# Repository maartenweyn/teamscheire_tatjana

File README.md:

# Team Scheire Tatjana - Tinnitus

Aflevering op VRTNu: [https://vrtnu.page.link/GqeyBG1gsRzztzNG9](https://vrtnu.page.link/GqeyBG1gsRzztzNG9)

Uitleg over de oplossing in deze podcast: [https://soundcloud.com/nerdlandmakertalk/09-maarten-weyn](https://soundcloud.com/nerdlandmakertalk/09-maarten-weyn)

# Geluidsmetingen

## 1. Wat is geluid?

**Geluid** is de **hoorbare verandering** van **luchtdruk** , of als je helemaal volledig wil zijn de verandering van de **dichtheid** van een **elastisch medium** , dat kan een **gas** zijn, een **vloeistof** of een **vaste** stof. En een geluidsbron veroorzaak verandering in de luchtdruk die zich in een golfbeweging door de lucht voortbewegen. Een luidspreker bijvoorbeeld zet een elektrisch signaal om in een beweging van een membraan. Die beweging zal dan een verandering in de luchtdruk veroorzaken.

Geluidsgolven tussen 20 Hz en 20 kHz, m.a.w. golven die 20 tot 20 000 keer per seconde bewegen kunnen door de mensen worden waargenomen. Boven 20 kHz hebben we wat we ultrasoon noemen.

Wist je dat geluid zich in lucht (bij 20°C en op zeeniveau) met ongeveer 343 m/s (of 1230 km/u) voortbeweegt, en in water van 20°C zelfs met 1482 m/s.

## 2. Wat is dan de geluidssterkte?

De **geluidsdruk** is het lokale drukverschil t.o.v. de atmosferische luchtdruk ten gevolge van een geluidsgolf. En dat wordt typisch in Pascal uitgedrukt.

Dit verschil wordt over een zeer kleine periode uitgemiddeld, men berekent de &quot;root mean square&quot; of de wortel van het gemiddelde van het kwadraat. Deze variatie is typisch zeer klein, de laagste waarde die nog hoorbaar is, is rond 2 \* 10-5 of 0.00002 Pa terwijl een explosie ongeveer 104 of 10000 kan zijn.

Daarom gebruik met een logaritmes waarde om de geluidsruk uit te drukken en dat noemen het **geluidsniveau** of Sound Pressure Level (SPL) in dB:

Met p0 de referentieruk 2 x 10-5 Pa of 20 uPa, de gehoordrempel van een gemiddeld persoon bij een frequentie van 1000 Hz.

Dus deze waarde geeft een indicatie hoeveel keer het geluid luider is dan gehoordrempel.

## 3. Wat is een logaritme?

In het geval van een geluidsniveau wordt een logaritme gebruikt met grondtal 10. In dat geval is de logaritme van een getal het getal waartoe 10 moet worden verheven. de logaritme van 1000 is bijvoorbeeld 3 want 103 = 10 x 10 x 10 = 1000.

In het geval van het geluidsniveau berekenen we de logaritme van het aantal keer het geluid sterker is dan de gehoordrempel, en dat getal nog eens x 20.

## 4. Hoe kunnen we dat nu meten

We gaan dit meten met een MEMS microfoon. MEMS staat voor _microelectron-mechanical systems_ of hele kleine elektro-mechanische systemen. In een MEMS microfoon zit een zeer klein beweegbaar membraan, een klein gaatje (of meerdere) laten het toe dat de luchtdruk kan veranderen die door de geluidgolven worden veroorzaakt en een vaste structuur.

Diagram van een dwarssnede van een MEMS-microfoon (figuur van EDN)

MP34DT05TR microfoon

Door de geluidgolven zal het membraan gaan bewegen en het verschil in capaciteit tussen het membraan en de vaste structuur wordt omgezet naar een elektrisch signaal.

In de chip van de MEMS-microfoon kan dit verschil in een spanning rechtstreeks worden doorgegeven naar een microcontroller (in analoge MEMS-microfoons) of in een digitale kan ze omgezet worden aar een PDM signaal.

Een PDM staat voor pulse density modulation. Bij PDM wordt een analoog signaal omgezet naar een binair signaal. In plaats van het signaal om te zetten naar codewoorden, komt bij PDM de relatieve dichtheid van de pulsen overeen met de amplitude van het analoge signaal.

0101101111111111111101101010010000000000000100010011011101111111111111011010100100000000000000100101

Vertegenwoordigd bvb

Figuur van Wikipedia (Kaldosh)

Het geluid wordt in dit geval 16000 keer per seconden gemeten. De microfoon is gekalibreerd en meet een waarde 1642 bij 94 dbA. Daarnaast meten we ook een root mean square gemiddelde in plaats van een dbFS (full scale meting) en we moeten dit nog corrigeren.

double leq = 3.0103+ 94 + 20 \* log10(sqrt(sumsquare / total\_samples) / 1642);

Nu voor we de samples gebruiken wordt de gemeten waarde nog gewogen naar de frequenties waarvoor het menselijk oor gevoeliger is. Zo worden bvb tonen onder de 1000 verzwakt. Een toon van 10 Hz wordt 70 keer zwakker gehoord dan een toon van 1000 Hz. Hoeveel dit niet helemaal correct is gebruiken we wel de dB(A) omdat de normen en wetgeving ook gebruik maakt van deze gewogen waarden.

Figuur van Lindosland at English Wikipedia

Nu kunnen we bijvoorbeeld per seconden meten wat het geluidsniveau is. Maar eigenlijk zijn we niet op zoek naar het geluidsniveau zelf, maar wel naar de geluidsdosis.

## 5. Wat is de geluidsdosis?

Een **geluidsdosis** is het gemiddelde geluidsniveau over een bepaalde (langere periode), bijvoorbeeld 8 uur of 24 uur. De WHO (wereld gezondheidsorganisatie) zegt dat deze normen voor 8u 80 dbA zijn en voor 24u 75 dbA.

Qua energieverbruik en dataopslag kunnen we uiteraard niet 8 u geluid gaan opnemen maar nemen we elke 10 seconden een sample van 1 seconde. Daarop bereken we het geluidsniveau. Daarna middelen we dit uit over 8u en 24u.

Je mag niet de gemiddeld van de dBA waarden nemen, dit zijn immers gemiddelde. Maar zetten de waardes eerst terug om naar de geluidsdruk en berekenen dan hoeveel % we reeds hebben ten opzichte van de herberekende waarde. Zo krijgen we 2 percentages die ook intuïtiever kunnen gebruikt worden door de gebruiker van het systeem.

# Wat staat er in de repo

* In **tizen** staat de oorspronkelijk ontwikkeling voor de Samsung Watch.
* In **hardware** het schema en PCB van de ontwikkelde wearble mee ontwikkeld door Kwinten Schram.
* In **3DModel** de stl van de gebruikte behuizing
* In **Arduino** een aantal test applicaties
* In **cordova** de cordova applicatie voor iOS
* In **Firmware** de code voor de wearable

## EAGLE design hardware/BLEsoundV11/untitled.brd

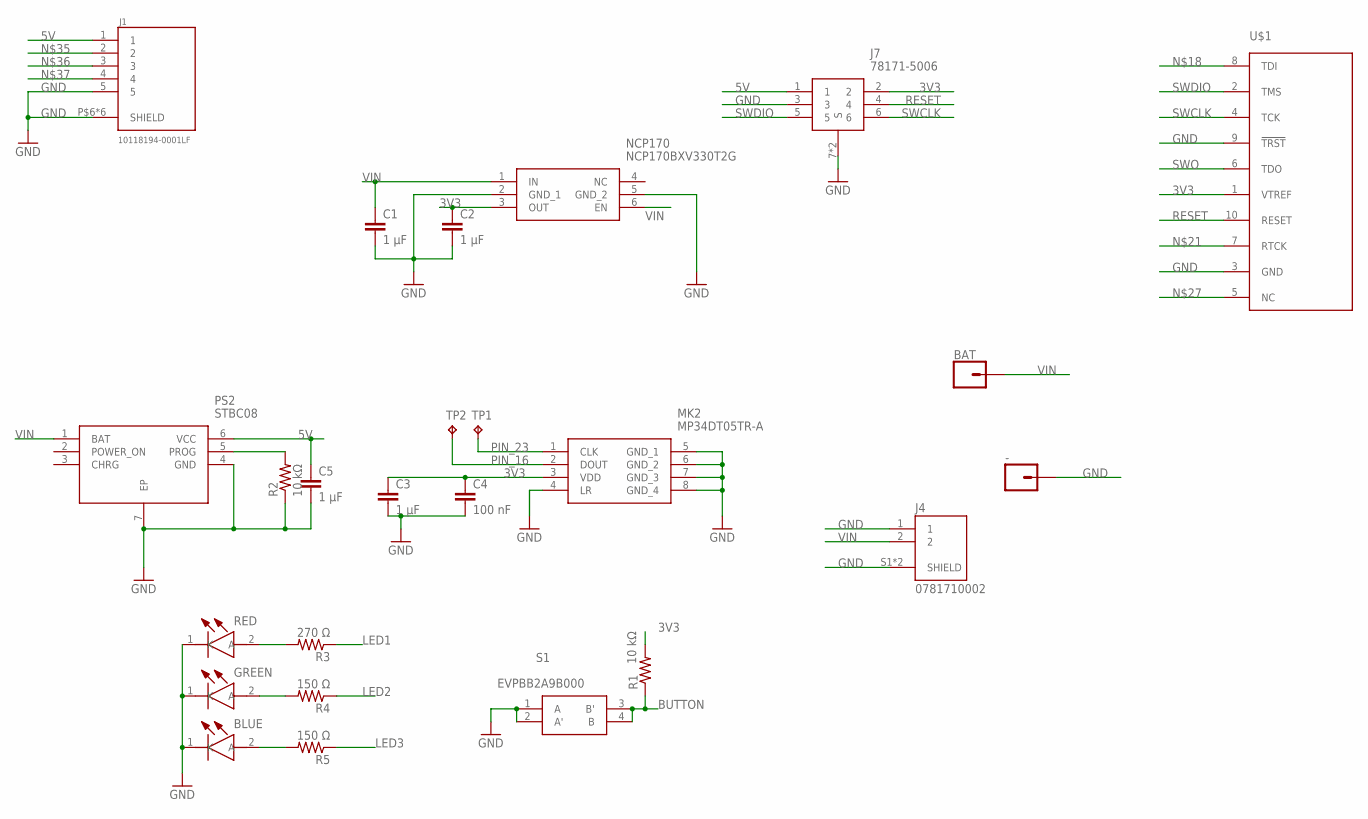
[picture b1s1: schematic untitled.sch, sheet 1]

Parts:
-: CONN_01; 1X01
BAT: CONN_01; 1X01
BLUE: 150040GS73220; LEDC1005X50N
C1, C2, C3, C5: 1 µF; SPARKFUN_0402-CAP
C4: 100 nF; SPARKFUN_0402-CAP
GREEN: 150040GS73220; LEDC1005X50N
J1: 10118194-0001LF; AMPHENOL_10118194-0001LF
J4: 0781710002; MOLEX_0781710002
J7: 78171-5006
MK2: MP34DT05TR-A; MP34DT05TRA
NCP170: NCP170BXV330T2G; SOTFL50P160X60-6N
PS2: STBC08; SON95P300X300X100-7N
R1, R2: 10 kΩ; SPARKFUN_0402-RES
R3: 270 Ω; SPARKFUN_0402-RES
R4, R5: 150 Ω; SPARKFUN_0402-RES
RED: 150040GS73220; LEDC1005X50N
S1: EVPBB2A9B000
TP1, TP2: TPTP06R; TP06R
U$1: TC2050-NL-MCP-NL; TC2030-MCP-NL

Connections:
3V3: C2.1, C3.1, C4.1, J7.2, MK2.3 (VDD), NCP170.3 (OUT), R1.2, U$1.1 (VTREF); also elsewhere on the board
5V: C5.1, J1.1, J7.1, PS2.6 (VCC)
BUTTON: R1.1, S1.3 (B'), S1.4 (B); also elsewhere on the board
GND: -.1, BLUE.1 (K), C1.2, C2.2, C3.2, C4.2, C5.2, GREEN.1 (K), J1.5, J1.P$6 (SHIELD), J1.P$7 (SHIELD), J1.P$8 (SHIELD), J1.P$9 (SHIELD), J1.P$10 (SHIELD), J1.P$11 (SHIELD), J4.1, J4.S1 (SHIELD), J4.S2 (SHIELD), J7.3, J7.7 (S), J7.8 (S), MK2.4 (LR), MK2.5 (GND_1), MK2.6 (GND_2), MK2.7 (GND_3), MK2.8 (GND_4), NCP170.2 (GND_1), NCP170.5 (GND_2), PS2.4 (GND), PS2.7 (EP), R2.1, RED.1 (K), S1.1 (A), S1.2 (A'), U$1.3 (GND), U$1.9 (!TRST); also elsewhere on the board
LED1: R3.1; also elsewhere on the board
LED2: R4.1; also elsewhere on the board
LED3: R5.1; also elsewhere on the board
unnamed: R3.2, RED.2 (A)
unnamed: GREEN.2 (A), R4.2
unnamed: BLUE.2 (A), R5.2
unnamed: PS2.5 (PROG), R2.2
PIN_16: MK2.2 (DOUT), TP2.TP; also elsewhere on the board
PIN_23: MK2.1 (CLK), TP1.TP; also elsewhere on the board
RESET: J7.4, U$1.10 (RESET); also elsewhere on the board
SWCLK: J7.6, U$1.4 (TCK); also elsewhere on the board
SWDIO: J7.5, U$1.2 (TMS); also elsewhere on the board
SWO: U$1.6 (TDO); also elsewhere on the board
VIN: BAT.1, C1.1, J4.2, NCP170.1 (IN), NCP170.6 (EN), PS2.1 (BAT)

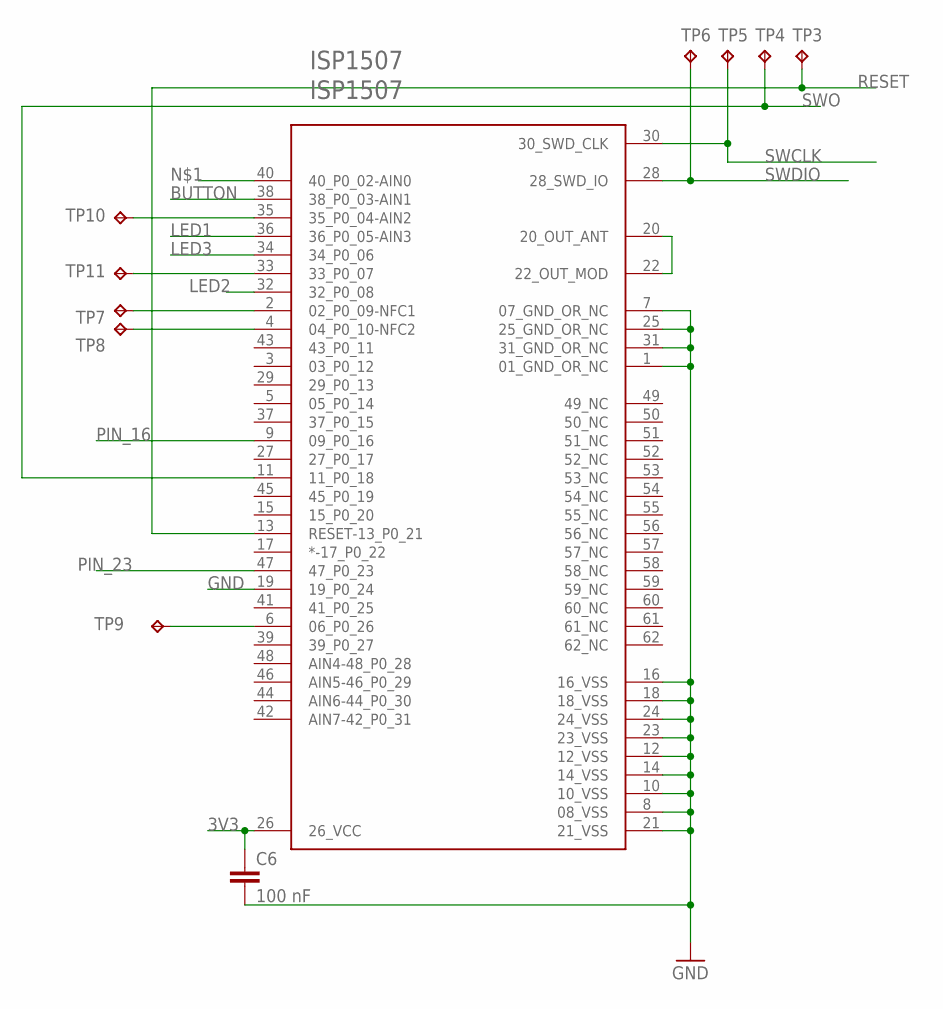
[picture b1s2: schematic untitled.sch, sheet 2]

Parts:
C6: 100 nF; SPARKFUN_0402-CAP
ISP1507: ISP1507
TP3, TP4, TP5, TP6, TP7, TP8, TP9, TP10, TP11: TPTP06R; TP06R

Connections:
3V3: C6.1, ISP1507.26 (26_VCC); also elsewhere on the board
BUTTON: ISP1507.38 (38_P0_03-AIN1); also elsewhere on the board
GND: C6.2, ISP1507.1 (01_GND_OR_NC), ISP1507.7 (07_GND_OR_NC), ISP1507.8 (08_VSS), ISP1507.10 (10_VSS), ISP1507.12 (12_VSS), ISP1507.14 (14_VSS), ISP1507.16 (16_VSS), ISP1507.18 (18_VSS), ISP1507.19 (19_P0_24), ISP1507.21 (21_VSS), ISP1507.23 (23_VSS), ISP1507.24 (24_VSS), ISP1507.25 (25_GND_OR_NC), ISP1507.31 (31_GND_OR_NC); also elsewhere on the board
LED1: ISP1507.36 (36_P0_05-AIN3); also elsewhere on the board
LED2: ISP1507.32 (32_P0_08); also elsewhere on the board
LED3: ISP1507.34 (34_P0_06); also elsewhere on the board
unnamed: ISP1507.6 (06_P0_26), TP9.TP
unnamed: ISP1507.2 (02_P0_09-NFC1), TP7.TP
unnamed: ISP1507.4 (04_P0_10-NFC2), TP8.TP
unnamed: ISP1507.35 (35_P0_04-AIN2), TP10.TP
unnamed: ISP1507.33 (33_P0_07), TP11.TP
unnamed: ISP1507.20 (20_OUT_ANT), ISP1507.22 (22_OUT_MOD)
PIN_16: ISP1507.9 (09_P0_16); also elsewhere on the board
PIN_23: ISP1507.47 (47_P0_23); also elsewhere on the board
RESET: ISP1507.13 (RESET-13_P0_21), TP3.TP; also elsewhere on the board
SWCLK: ISP1507.30 (30_SWD_CLK), TP5.TP; also elsewhere on the board
SWDIO: ISP1507.28 (28_SWD_IO), TP6.TP; also elsewhere on the board
SWO: ISP1507.11 (11_P0_18), TP4.TP; also elsewhere on the board

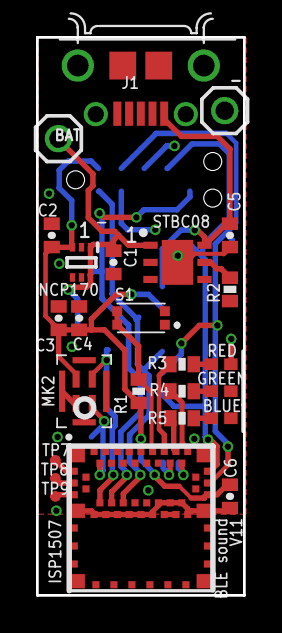
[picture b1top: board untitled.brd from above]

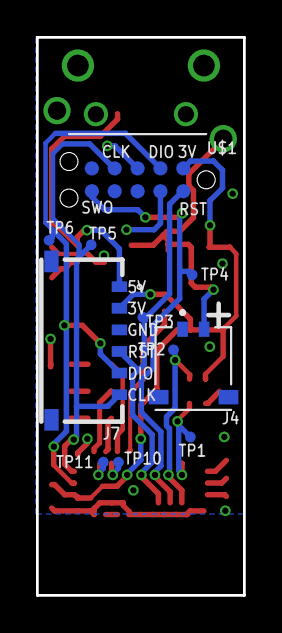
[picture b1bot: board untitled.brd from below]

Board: 2 copper layers, 11.5 x 31.0 mm, 36 parts (11 on the bottom side), 24 nets.

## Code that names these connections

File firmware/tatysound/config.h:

#include <ble_types.h>

#include <app_timer.h>

#define ODR 200

#define ACC_TIMER_INTERVAL              1000/ODR                       /**< interval (msecs). */

#define ACC_LIST_SIZE 40 // restricted by max size of ble

#define I2S_BUFFER_SIZE     2000
#define SHORT_SAMPLE        16000
#define SKIP_BUFFERS        1
#define SAMPLE_RATE   16000//15650
#define CLOCK_PERIOD        16000000/(64*SAMPLE_RATE) 
#define MAX_BLE_DATA  1440
#define BLE_DATA_FREE  60 //if buffer full free 1 hour
#define MAX_BLE_DATA_THRESHOLD  0 //50

#define SOUND_TIMER_INTERVAL_SEC  10
#define SOUND_TIMER_INTERVAL  SOUND_TIMER_INTERVAL_SEC*1000

//PCM 
#define CONFIG_IO_PDM_CLK		23
#define CONFIG_IO_PDM_DATA		16
//#define CONFIG_IO_PDM_DATA		26

#define CONFIG_AUDIO_PDM_GAIN 		0x38
#define CONFIG_AUDIO_FRAME_SIZE_BYTES   64
#define CONFIG_AUDIO_FRAME_SIZE_SAMPLES 64
#define CONFIG_PDM_FRAME_SIZE_SAMPLES	64
#define CONFIG_AUDIO_FRAME_BUFFERS 	16

#define SOUND_BUFFER_SIZE     2000

// ADUIO PROCESSING
#define MIC_OFFSET_DB     3.0103    // Default offset (sine-wave RMS vs. dBFS)
#define MIC_REF_DB        94.0      // dB(SPL)
  #define MIC_REF_AMPL      1642 //Amplitude at 94dB(SPL) (-26dBFS from datasheet, i.e. (2^15-1)*10^(-26/20) )
//#define MIC_REF_AMPL      6569 //Amplitude at 94dB(SPL) (-26dBFS from datasheet, i.e. (2^17-1)*10^(-26/20) )
//#define MIC_REF_AMPL  0.050118723362727

// BLE

#define APP_BLE_CONN_CFG_TAG            1                                           /**< A tag identifying the SoftDevice BLE configuration. */
#define APP_BLE_OBSERVER_PRIO           3                                           /**< Application's BLE observer priority. You shouldn't need to modify this value. */

#define DEVICE_NAME                     "TatySound"                                    /**< Name of device. Will be included in the advertising data. */
#define NUS_SERVICE_UUID_TYPE           BLE_UUID_TYPE_VENDOR_BEGIN                  /**< UUID type for the Nordic UART Service (vendor specific). */

#define MIN_CONN_INTERVAL               MSEC_TO_UNITS(20, UNIT_1_25_MS)             /**< Minimum acceptable connection interval (20 ms), Connection interval uses 1.25 ms units. */
#define MAX_CONN_INTERVAL               MSEC_TO_UNITS(75, UNIT_1_25_MS)             /**< Maximum acceptable connection interval (75 ms), Connection interval uses 1.25 ms units. */
#define SLAVE_LATENCY                   0                                           /**< Slave latency. */
#define CONN_SUP_TIMEOUT                MSEC_TO_UNITS(4000, UNIT_10_MS)             /**< Connection supervisory timeout (4 seconds), Supervision Timeout uses 10 ms units. */
#define FIRST_CONN_PARAMS_UPDATE_DELAY  APP_TIMER_TICKS(5000)                       /**< Time from initiating event (connect or start of notification) to first time sd_ble_gap_conn_param_update is called (5 seconds). */
#define NEXT_CONN_PARAMS_UPDATE_DELAY   APP_TIMER_TICKS(30000)                      /**< Time between each call to sd_ble_gap_conn_param_update after the first call (30 seconds). */
#define MAX_CONN_PARAMS_UPDATE_COUNT    3                                           /**< Number of attempts before giving up the connection parameter negotiation. */

#define APP_BLE_OBSERVER_PRIO           3                                           /**< Application's BLE observer priority. You shouldn't need to modify this value. */

#define APP_ADV_INTERVAL                64                                          /**< The advertising interval (in units of 0.625 ms. This value corresponds to 40 ms). */
#define APP_ADV_DURATION                10//18000                                       /**< The advertising duration (180 seconds) in units of 10 milliseconds. */

#define SLOW_APP_ADV_INTERVAL           1600   //1000 ms * 1.6
#define SLOW_APP_ADV_TIMEOUT_IN_SECONDS 0


// Buttons
#define BUTTON1 3

// LEDS

#define LED1  5
#define LED2  8
#define LED3  6

#define LED_RED LED1
#define LED_GREEN LED2
#define LED_BLUE LED3

#define LED_INDICATE_SENT_OK               0
#define LED_INDICATE_SEND_ERROR            0
#define LED_INDICATE_RCV_OK                0
#define LED_INDICATE_RCV_ERROR             0
#define LED_INDICATE_CONNECTED             LED_BLUE
#define LED_INDICATE_BONDING               0
#define LED_INDICATE_ADVERTISING_DIRECTED  0
#define LED_INDICATE_ADVERTISING_SLOW      0
#define LED_INDICATE_ADVERTISING_WHITELIST 0
#define LED_INDICATE_ADVERTISING  0

#define LED_INDICATE_TX  0


#define RED 1
#define GREEN 2
#define BLUE  4
#define WHITE 7

#define RED_ID   0
#define GREEN_ID 1
#define BLUE_ID  2


#define LED_BRIGHTNESS  10


#define ADVERTISING_LED_ON_INTERVAL             100
#define ADVERTISING_LED_OFF_INTERVAL            4900

#define CONNECTED_LED_ON_INTERVAL               100
#define CONNECTED_LED_OFF_INTERVAL              3000

#define ADVERTISING_DIRECTED_LED_ON_INTERVAL   200
#define ADVERTISING_DIRECTED_LED_OFF_INTERVAL  200

#define ADVERTISING_WHITELIST_LED_ON_INTERVAL  200
#define ADVERTISING_WHITELIST_LED_OFF_INTERVAL 800

#define ADVERTISING_SLOW_LED_ON_INTERVAL       400
#define ADVERTISING_SLOW_LED_OFF_INTERVAL      4000

#define BONDING_INTERVAL                       100

#define SENT_OK_INTERVAL                       100
#define SEND_ERROR_INTERVAL                    500

#define RCV_OK_INTERVAL                        100
#define RCV_ERROR_INTERVAL                     500

#define ALERT_INTERVAL                         200

#define LIGHT_BUTTON_CHANGE_INTERVAL            1000
#define BUTTON_TIMEOUT_INTERVAL                 10000
#define BUTTON_ACK_FLASH_INTERVAL               500

extern uint8_t sleep_status;

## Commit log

2019-05-12 cleaning up
2019-05-12 testing to solve 2 permissions
2019-05-16 matlab calculation of Leq
2019-05-21 working db version
2019-05-22 demo version to bart vinck
2019-05-25 continous sending - pauzes when in sleep
2019-05-28 service and viewer
2019-06-05 queues data when no connection
2019-06-16 working basis version
2019-06-18 working on web viewer
2019-06-20 working app
2019-06-23 working version sending to private server
2019-06-23 visualizing all indicators
2019-06-23 updated calibration
2019-06-23 version of beta
2019-06-24 v1.0.4
2019-06-24 data storage fix because of curl timeout
2019-06-24 increase version 1.0.5
2019-09-27 initial commit app
2019-09-28 background service is working
2019-10-01 arduino mems mic
2019-10-01 st bleumic cmakefile building
2019-10-28 working version on esp32
2019-10-28 datasheet
2019-10-28 adding nrf software
2019-10-30 trying to sync pwm clocks
2019-10-30 failing to get it to work
2019-11-03 ready for testing prototype
2019-11-05 optimizing ble
2019-11-06 working with STM mic
2019-11-07 fixed timestamp
2019-11-09 working prototype need to fix http upload when offline
2019-11-20 chaning storage
2019-12-06 adapting app
2019-12-06 addapting to new sdk
2019-12-06 working with db on app
2019-12-06 adapting firmware to new hardware
2019-12-06 new hardware schematics
2019-12-06 working version with graph
2019-12-06 back working on windows
2019-12-07 working on ios
2019-12-07 platforms in gitignore
2019-12-09 gui ok on ios
2019-12-09 tx on connect
2019-12-10 version pushed on flightcase
2019-12-10 adapted based on app store feedback
2019-12-19 optimized db load
2020-01-12 last version
2020-05-18 Bump is-my-json-valid
    Bumps [is-my-json-valid](https://github.com/mafintosh/is-my-json-valid) from 2.15.0 to 2.20.0.
    - [Release notes](https://github.com/mafintosh/is-my-json-valid/releases)
    - [Commits](https://github.com/mafintosh/is-my-json-valid/compare/v2.15.0...v2.20.0)
2020-05-18 Bump stringstream
    Bumps [stringstream](https://github.com/mhart/StringStream) from 0.0.5 to 0.0.6.
    - [Release notes](https://github.com/mhart/StringStream/releases)
    - [Commits](https://github.com/mhart/StringStream/compare/v0.0.5...v0.0.6)
2020-05-18 Bump sshpk in /cordova/TatySound/www/lib/OnsenUI/css-components-src
    Bumps [sshpk](https://github.com/joyent/node-sshpk) from 1.10.2 to 1.16.1.
    - [Release notes](https://github.com/joyent/node-sshpk/releases)
    - [Commits](https://github.com/joyent/node-sshpk/compare/v1.10.2...v1.16.1)
2020-10-12 v1.0.6
2020-10-12 Bump is-my-json-valid
    Bumps [is-my-json-valid](https://github.com/mafintosh/is-my-json-valid) from 2.15.0 to 2.20.5.
    - [Release notes](https://github.com/mafintosh/is-my-json-valid/releases)
    - [Commits](https://github.com/mafintosh/is-my-json-valid/compare/v2.15.0...v2.20.5)
2020-10-15 added icons
2020-10-30 added fusion360 file
2022-10-31 Delete cordova/TatySound/www/lib/OnsenUI directory
    Removing OnsenUI library from repository

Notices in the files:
parts and their libraries:
TC2050: ©2009 ROFA.cz
SparkFun-Connectors: Licensing: Creative Commons ShareAlike 4.0 International - https://creativecommons.org/licenses/by-sa/4.0
